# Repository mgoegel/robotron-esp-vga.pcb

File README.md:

# Robotron VGA Adapter PCB

This project is based on the work of Stefan "Ordoban" Berndt.

ESP32S3 based MDA to VGA adapter

{width=300px} {width=300px}

{width=300px} {width=300px}

[Schematics](pc1715-esp32vga/schematics/pc1715-esp32vga.pdf)

Supported systems: <br>
[Connection A7100](Connections.md)
* A7100 
* A7150/CM1910 Text-only
* EC1834 MON Adapter (K7228.1, K7229.21-.24, Alpha 1 Monitor replacement)

[Connection PC1715](Connections.md)
* PC1715 
* A5120/K8924
* MC 80.30

[Connection VIDEO3/NANOS](Connections.md)
* NANOS

Published at: https://www.robotrontechnik.de/html/forum/thwb/showtopic.php?threadid=21380

The software is here: https://github.com/mgoegel/robotron-esp-vga

An (little bit outdated) order list is available at reichelt: https://www.reichelt.de/my/2181752<br>
I'll add mouser, as soon as I found out, how to publish the list... ;-)

Also you can find the BOM for both PCBs
* [Main board](pc1715-esp32vga/bom/ibom.html)
* [Keypad](esp32vga-keypad/bom/ibom.html)

### Main Board PIN Connector PINOUT

#### VGA J2 (D-SUB 15HD) / J5 (IDC16_VGA)

| D_SUB 15 HD | Signal | Pin | Pin | Signal | D_SUB 15 HD |
| ----------- | ------ | --- | --- | ------ | ----------- |
| 1           | RED    | 1   | 2   | GREEN  | 2           |
| 3           | BLUE   | 3   | 4   | NC     |             |
| 6           | GND    | 5   | 6   | GND    | 5           |
| 7           | GND    | 7   | 8   | GND    | 10          |
| 8           | GND    | 9   | 10  | GND    | NC          |
|             | NC     | 11  | 12  | NC     |             |
| 13          | HSYNC  | 13  | 14  | VSYNC  | 14          |
|             | NC     | 15  | 16  | NC     |             |

#### VIDEO IN J1

| Signal      | Pin | Pin | Signal |
| ----------- | --- | --- | ------ |
| 5V IN       | 1   | 2   | 5V IN  |
| 3.3V IN/OUT | 3   | 4   | VIDEO  |
| GND         | 5   | 6   | INTENS |
| GND         | 7   | 8   | GND    |
| GND         | 9   | 10  | BSYNC  |

#### KEYPAD J4

| Signal  | Pin | Pin | Signal  |
| ------- | --- | --- | ------- |
| K_DOWN  | 1   | 2   | K_RIGHT |
| K_UP    | 3   | 4   | K_LEFT  |
| L_STAT  | 5   | 6   | L_SYNC  |
| RST     | 7   | 8   | NC      |
| 3.3V    | 9   | 10  | GND     |

#### DEBUG J7 2x04

| Signal | Pin | Pin | Signal |
| ------ | --- | --- | ------ |
| TP-SPI | 1   | 2   | TP-CPY |
| TP-11  | 3   | 4   | TP-12  |
| INTENS | 5   | 6   | VIDEO  |
| BSYNC  | 7   | 8   | GND    |

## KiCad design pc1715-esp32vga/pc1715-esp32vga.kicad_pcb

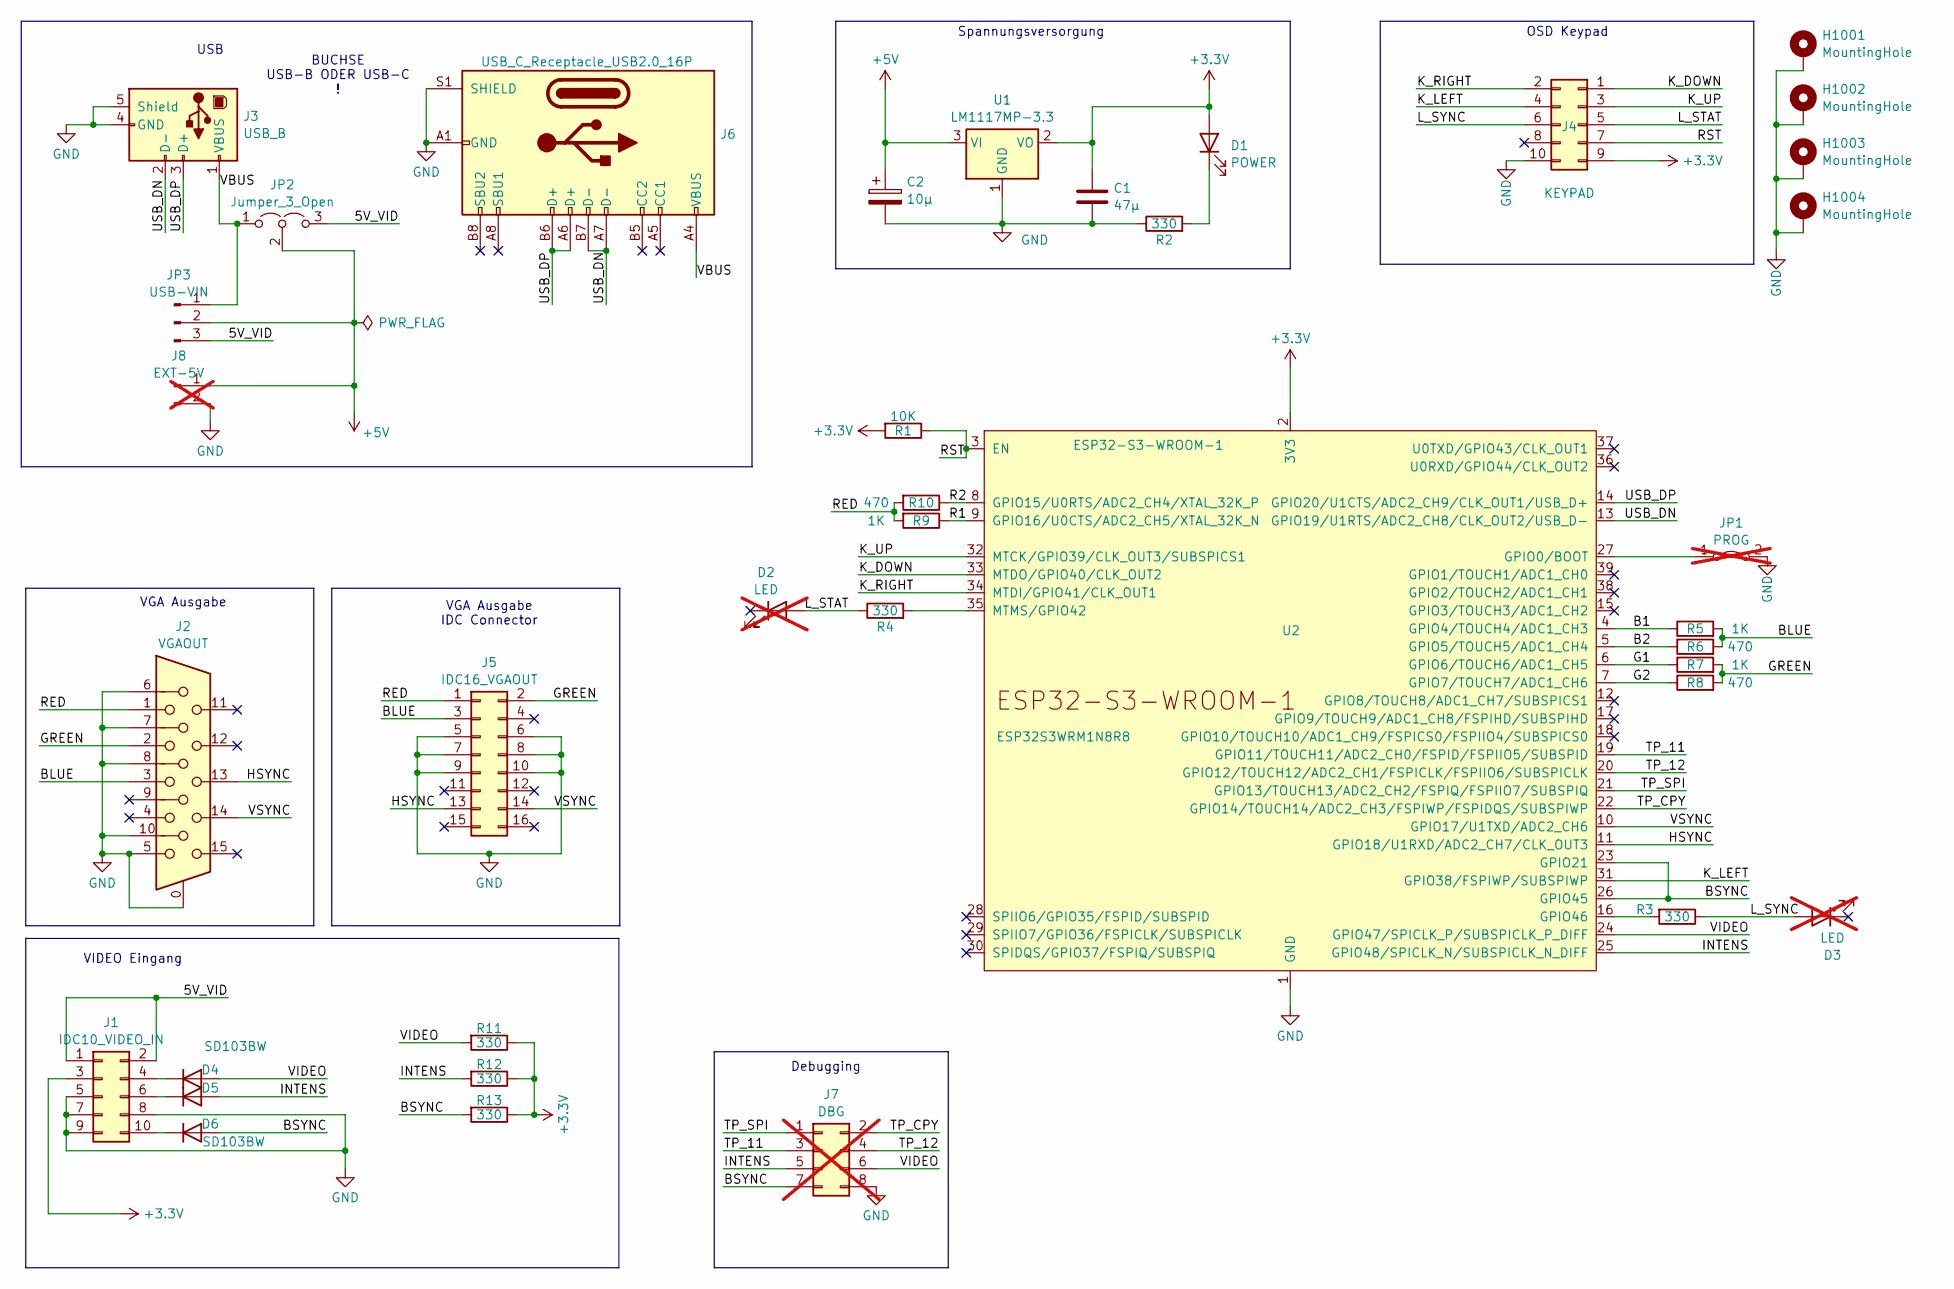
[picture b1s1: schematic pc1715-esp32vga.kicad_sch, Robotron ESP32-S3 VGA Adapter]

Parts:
C1: 47µ; CP_EIA-3528-21_Kemet-B_Pad1.50x2.35mm_HandSolder
C2: 10µ; CP_EIA-3528-21_Kemet-B_Pad1.50x2.35mm_HandSolder
D1: POWER; D_0805_2012Metric_Pad1.15x1.40mm_HandSolder
D2, D3: LED; not fitted
D4, D5, D6: SD103BW; D_SOD-123
H1001, H1002, H1003, H1004: MountingHole; MountingHole_3.2mm_M3_ISO7380_Pad
J1: IDC10_VIDEO_IN; IDC-Header_2x05_P2.54mm_Vertical
J2: VGAOUT; TE_1-1734530-1
J3: USB_B; USB_B_Lumberg_2411_02_Horizontal
J4: KEYPAD; IDC-Header_2x05_P2.54mm_Vertical
J5: IDC16_VGAOUT; IDC-Header_2x08_P2.54mm_Vertical
J6: USB_C_Receptacle_USB2.0_16P; USB_C_Receptacle_GCT_USB4105-xx-A_16P_TopMnt_Horizontal
J7: DBG; PinHeader_2x04_P2.54mm_Vertical; not fitted
J8: EXT-5V; PinHeader_1x02_P2.54mm_Vertical; not fitted
JP1: PROG; PinHeader_1x02_P2.54mm_Vertical; not fitted
JP2: Jumper_3_Open; SolderJumper-3_P1.3mm_Open_RoundedPad1.0x1.5mm_NumberLabels
JP3: USB-VIN; PinHeader_1x03_P2.54mm_Vertical
R1: 10K; R_0805_2012Metric_Pad1.20x1.40mm_HandSolder
R2, R3, R4, R11, R12, R13: 330; R_0805_2012Metric_Pad1.20x1.40mm_HandSolder
R5, R7, R9: 1K; R_0805_2012Metric_Pad1.20x1.40mm_HandSolder
R6, R8, R10: 470; R_0805_2012Metric_Pad1.20x1.40mm_HandSolder
U1: LM1117MP-3.3; SOT-223-3_TabPin2
U2: ESP32-S3-WROOM-1

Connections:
+3.3V: C1.1, D1.2 (A), J1.3, J4.9, R1.2, R11.1, R12.1, R13.1, U1.2 (VO), U2.2 (3V3)
+5V: C2.1, J8.1, JP2.2 (C), JP3.2, U1.3 (VI)
/5V_VID: J1.1, J1.2, JP2.3 (B), JP3.3
/B1: R5.1, U2.4 (GPIO4/TOUCH4/ADC1_CH3)
/B2: R6.1, U2.5 (GPIO5/TOUCH5/ADC1_CH4)
/BLUE: J2.3, J5.3, R5.2, R6.2
/BSYNC: D6.2 (A), J7.7, R13.2, U2.23 (GPIO21), U2.26 (GPIO45)
/G1: R7.1, U2.6 (GPIO6/TOUCH6/ADC1_CH5)
/G2: R8.1, U2.7 (GPIO7/TOUCH7/ADC1_CH6)
/GREEN: J2.2, J5.2, R7.2, R8.2
/HSYNC: J2.13, J5.13, U2.11 (GPIO18/U1RXD/ADC2_CH7/CLK_OUT3)
/INTENS: D5.2 (A), J7.5, R12.2, U2.25 (GPIO48/SPICLK_N/SUBSPICLK_N_DIFF)
/K_DOWN: J4.1, U2.33 (MTDO/GPIO40/CLK_OUT2)
/K_LEFT: J4.4, U2.31 (GPIO38/FSPIWP/SUBSPIWP)
/K_RIGHT: J4.2, U2.34 (MTDI/GPIO41/CLK_OUT1)
/K_UP: J4.3, U2.32 (MTCK/GPIO39/CLK_OUT3/SUBSPICS1)
/L_STAT: D2.2 (A), J4.5, R4.1
/L_SYNC: D3.2 (A), J4.6, R3.1
/R1: R9.1, U2.9 (GPIO16/U0CTS/ADC2_CH5/XTAL_32K_N)
/R2: R10.1, U2.8 (GPIO15/U0RTS/ADC2_CH4/XTAL_32K_P)
/RED: J2.1, J5.1, R9.2, R10.2
/RST: J4.7, R1.1, U2.3 (EN)
/TP_11: J7.3, U2.19 (GPIO11/TOUCH11/ADC2_CH0/FSPID/FSPIIO5/S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)
/TP_12: J7.4, U2.20 (GPIO12/TOUCH12/ADC2_CH1/FSPICLK/FSPIIO6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)
/TP_CPY: J7.2, U2.22 (GPIO14/TOUCH14/ADC2_CH3/FSPIWP/FSPIDQS/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)
/TP_SPI: J7.1, U2.21 (GPIO13/TOUCH13/ADC2_CH2/FSPIQ/FSPIIO7/S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)
/USB_DN: J3.2 (D-), J6.A7 (D-), J6.B7 (D-), U2.13 (GPIO19/U1RTS/ADC2_CH8/CLK_OUT2/USB_D-)
/USB_DP: J3.3 (D+), J6.A6 (D+), J6.B6 (D+), U2.14 (GPIO20/U1CTS/ADC2_CH9/CLK_OUT1/USB_D+)
/VBUS: J3.1 (VBUS), J6.A4 (VBUS), J6.A9 (VBUS), J6.B4 (VBUS), J6.B9 (VBUS), JP2.1 (A), JP3.1
/VIDEO: D4.2 (A), J7.6, R11.2, U2.24 (GPIO47/SPICLK_P/SUBSPICLK_P_DIFF)
/VSYNC: J2.14, J5.14, U2.10 (GPIO17/U1TXD/ADC2_CH6)
GND: C1.2, C2.2, H1001.1, H1002.1, H1003.1, H1004.1, J1.5, J1.7, J1.8, J1.9, J2.0, J2.5, J2.6, J2.7, J2.8, J2.10, J3.4 (GND), J3.5 (Shield), J4.10, J5.5, J5.6, J5.7, J5.8, J5.9, J5.10, J6.A1 (GND), J6.A12 (GND), J6.B1 (GND), J6.B12 (GND), J6.S1 (SHIELD), J7.8, J8.2, JP1.2 (B), R2.1, U1.1 (GND), U2.1 (GND), U2.40 (GND), U2.41 (GND)
unnamed: D1.1 (K), R2.2
unnamed: D4.1 (K), J1.4
unnamed: D5.1 (K), J1.6
unnamed: D6.1 (K), J1.10
unnamed: JP1.1 (A), U2.27 (GPIO0/BOOT)
unnamed: R3.2, U2.16 (GPIO46)
unnamed: R4.2, U2.35 (MTMS/GPIO42)

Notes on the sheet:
VGA Ausgabe IDC Connector
Debugging
Spannungsversorgung
VIDEO Eingang
OSD Keypad
VGA Ausgabe
BUCHSE USB-B ODER USB-C !
USB

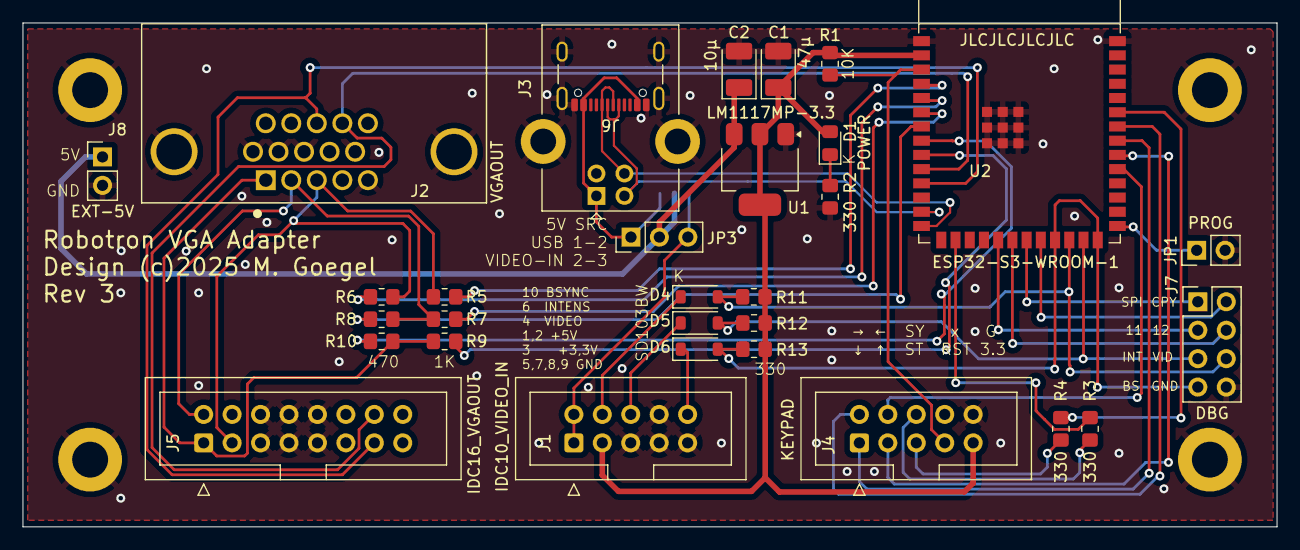
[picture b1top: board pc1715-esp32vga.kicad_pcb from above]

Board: 2 copper layers, 112.0 x 45.0 mm, 36 parts (1 on the bottom side), 39 nets.

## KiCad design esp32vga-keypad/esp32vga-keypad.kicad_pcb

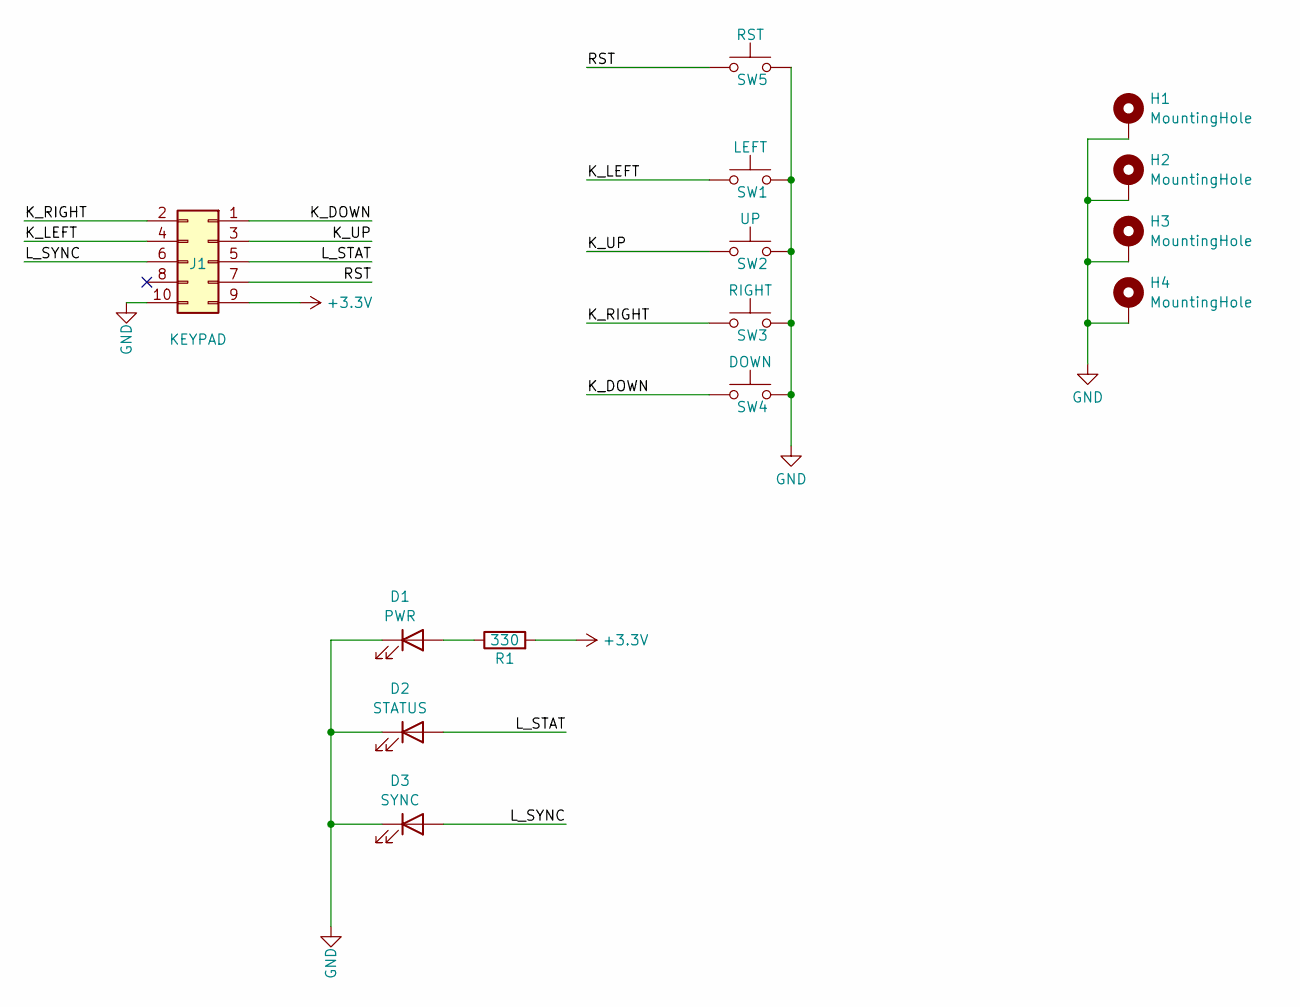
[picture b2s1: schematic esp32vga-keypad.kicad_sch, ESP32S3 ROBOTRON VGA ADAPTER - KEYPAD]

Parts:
D1: PWR; LED_0603_1608Metric_Pad1.05x0.95mm_HandSolder
D2: STATUS; LED_0603_1608Metric_Pad1.05x0.95mm_HandSolder
D3: SYNC; LED_0603_1608Metric_Pad1.05x0.95mm_HandSolder
H1, H2, H3, H4: MountingHole; MountingHole_3.2mm_M3_ISO7380_Pad
J1: KEYPAD; IDC-Header_2x05_P2.54mm_Horizontal
R1: 330; R_0805_2012Metric_Pad1.20x1.40mm_HandSolder
SW1: LEFT; SW_Push_TS04_NO_6x6mm_H5.00_BKXXX_SMT
SW2: UP; SW_Push_TS04_NO_6x6mm_H5.00_BKXXX_SMT
SW3: RIGHT; SW_Push_TS04_NO_6x6mm_H5.00_BKXXX_SMT
SW4: DOWN; SW_Push_TS04_NO_6x6mm_H5.00_BKXXX_SMT
SW5: RST; SW_Push_TS04_NO_6x6mm_H5.00_BKXXX_SMT

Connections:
+3.3V: J1.9, R1.2
/K_DOWN: J1.1, SW4.1
/K_LEFT: J1.4, SW1.1
/K_RIGHT: J1.2, SW3.1
/K_UP: J1.3, SW2.1
/L_STAT: D2.2 (A), J1.5
/L_SYNC: D3.2 (A), J1.6
/RST: J1.7, SW5.1
GND: D1.1 (K), D2.1 (K), D3.1 (K), H1.1, H2.1, H3.1, H4.1, J1.10, SW1.2, SW2.2, SW3.2, SW4.2, SW5.2
unnamed: D1.2 (A), R1.1

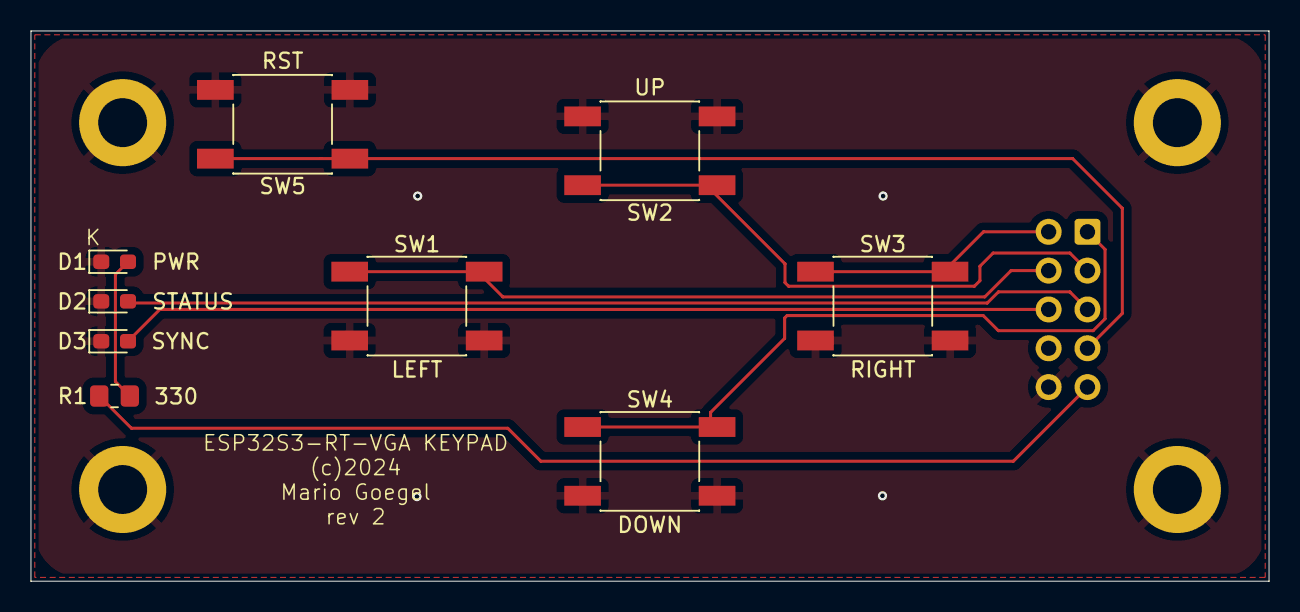
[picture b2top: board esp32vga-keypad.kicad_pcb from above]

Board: 2 copper layers, 81.0 x 36.0 mm, 14 parts (1 on the bottom side), 10 nets.

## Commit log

2024-03-14 Initial
2024-03-14 updated ignore
2024-03-14 remove old gitignore
2024-03-14 IDC10 Beschriftung
2024-04-21 Prototype #1 Gerber files added
2024-08-04 Revision 2
2024-09-07 Rev 2 Main PCB with keypad
2024-09-08 Documentation improved
2024-12-15 Silkscreen correction for J4 Changed BOOT jumper to PROG jumper, Connection to GND instead VCC
2025-03-06 Update to rev3
2025-06-22 Added PCB comments Saved in Kicad 9

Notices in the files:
esp32vga-keypad/esp32vga-keypad.kicad_pcb:
(c)2024
pc1715-esp32vga/pc1715-esp32vga.kicad_pcb:
Design (c)2025 M. Goegel
